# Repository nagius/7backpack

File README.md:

# 7Backpack

7Backpack is a shift register based led driver similar to [SparkFun Large Digit Driver](https://www.sparkfun.com/products/13279) but with a nicer form factor.

It has been designed to fit directly at the back of common anode 7-segments displays. Four sizes are supported : 1.5" (15101BS), 1.8" (18011BH), 2.3" (23011BH) and 3" (30101BS).

## Features

This board is functionnaly identical to SparkFun Large Digit Driver. Exact same code found at [Spakfun tutorial](https://learn.sparkfun.com/tutorials/large-digit-driver-hookup-guide/all) can be used without any modification.

The size of the board can be adjusted to match the size of the display. The PCB has pre-cut lines to snap unneeded pieces of the board.

## Manufacturing

See directory `Gerber/` for production files and bill of materials.

## License

Copyleft 2024 - Nicolas AGIUS

Creative Commons - Attribution-NonCommercial-ShareAlike 4.0 International (CC BY-NC-SA 4.0)

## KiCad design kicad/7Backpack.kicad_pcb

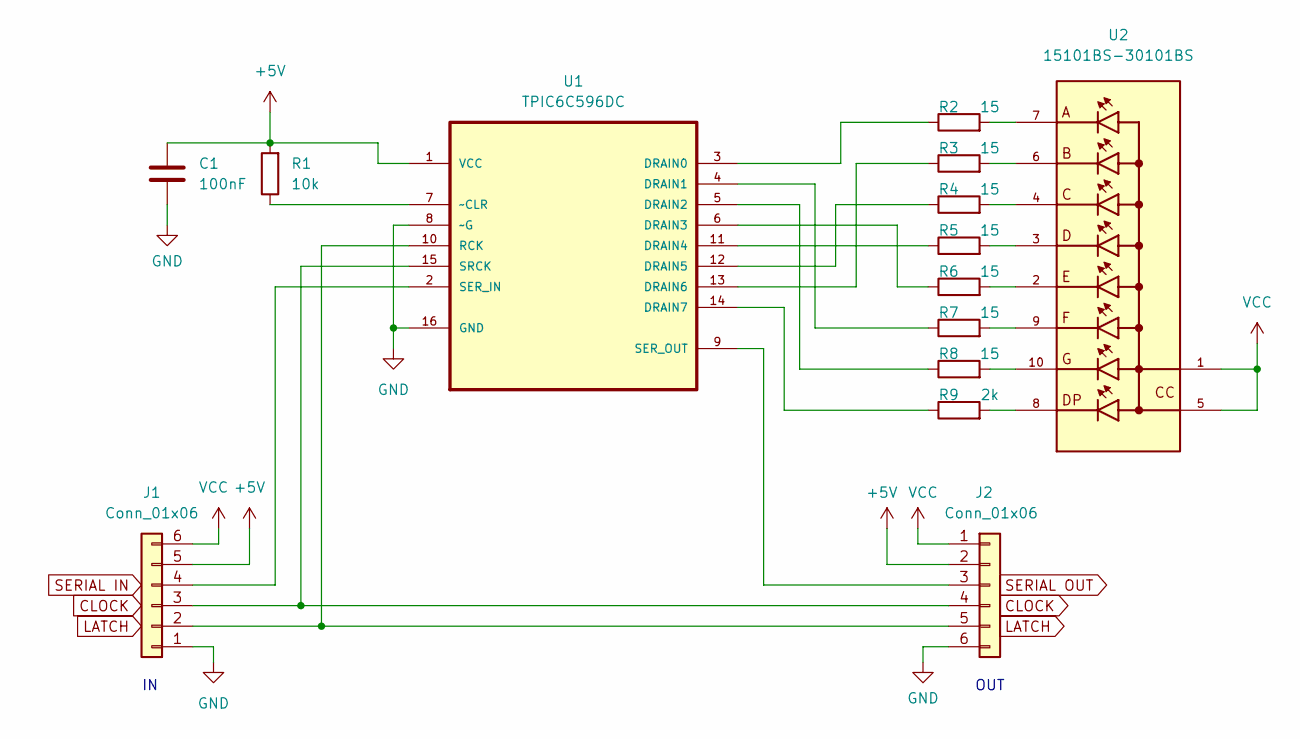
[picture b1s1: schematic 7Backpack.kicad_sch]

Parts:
C1: 100nF; C_0603_1608Metric; LCSC C14663
J1, J2: Conn_01x06; PinHeader_1x06_P2.54mm_Vertical
R1: 10k; R_0603_1608Metric; LCSC C25804
R2, R3, R4, R5, R6, R7, R8: 15; R_0603_1608Metric; LCSC C22810
R9: 2k; R_0603_1608Metric; LCSC C22975
U1: TPIC6C596DC; SOIC127P600X175-16N; LCSC C2872253
U2: 15101BS-30101BS

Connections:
+5V: C1.1, J1.5, J2.2, R1.2, U1.1 (VCC)
GND: C1.2, J1.1, J2.6, U1.8 (~G), U1.16 (GND)
unnamed: J1.2, J2.5, U1.10 (RCK)
unnamed: J1.3, J2.4, U1.15 (SRCK)
unnamed: J1.4, U1.2 (SER_IN)
unnamed: J2.3, U1.9 (SER_OUT)
unnamed: R1.1, U1.7 (~CLR)
unnamed: R2.1, U1.3 (DRAIN0)
unnamed: R2.2, U2.7
unnamed: R3.1, U1.13 (DRAIN6)
unnamed: R3.2, U2.6
unnamed: R4.1, U1.12 (DRAIN5)
unnamed: R4.2, U2.4
unnamed: R5.1, U1.11 (DRAIN4)
unnamed: R5.2, U2.3
unnamed: R6.1, U1.6 (DRAIN3)
unnamed: R6.2, U2.2
unnamed: R7.1, U1.4 (DRAIN1)
unnamed: R7.2, U2.9
unnamed: R8.1, U1.5 (DRAIN2)
unnamed: R8.2, U2.10
unnamed: R9.1, U1.14 (DRAIN7)
unnamed: R9.2, U2.8
VCC: J1.6, J2.1, U2.1, U2.5

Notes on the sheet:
OUT

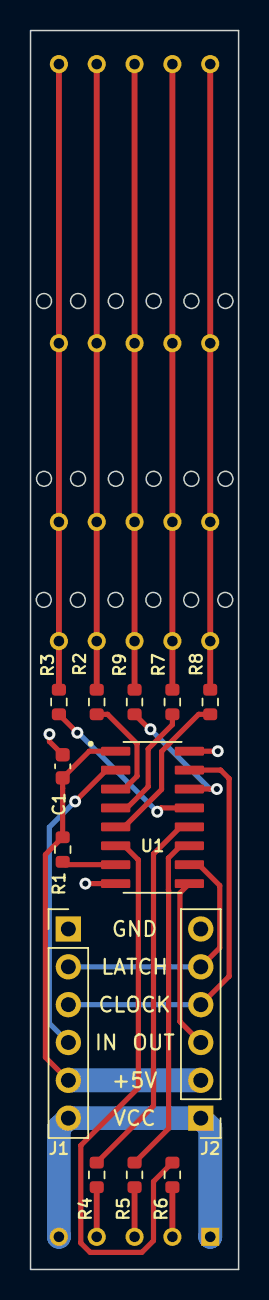
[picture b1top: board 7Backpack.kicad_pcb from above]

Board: 2 copper layers, 14.0 x 83.2 mm, 14 parts (1 on the bottom side), 24 nets.

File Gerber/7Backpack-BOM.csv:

Comment,Designator,Footprint,LCSC
"100nF","C1","Capacitor_SMD:C_0603_1608Metric","C14663"
"10k","R1","Resistor_SMD:R_0603_1608Metric","C25804"
"15","R2,R3,R4,R5,R6,R7,R8","Resistor_SMD:R_0603_1608Metric","C22810"
"2k","R9","Resistor_SMD:R_0603_1608Metric","C22975"
"TPIC6C596DC","U1","TPIC6C596DR:SOIC127P600X175-16N","C2872253"

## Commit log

2024-07-21 Initial draft
2024-07-21 Autorouted
2024-07-21 Finalized routing
2024-07-22 Updated silkscreen
2024-07-22 Added pre-cut
2024-07-31 AddedGerber files
2024-08-01 Switched to SOP-16
2024-08-01 Added datasheets
2024-09-03 Renamed directories
2024-09-03 Added readme
